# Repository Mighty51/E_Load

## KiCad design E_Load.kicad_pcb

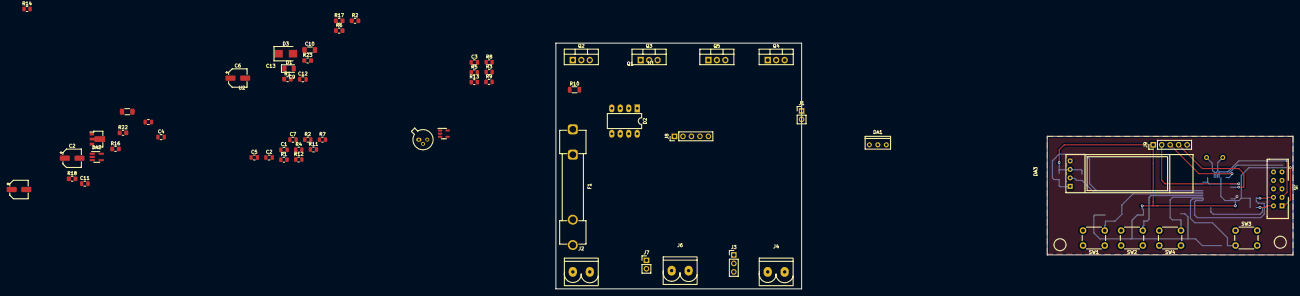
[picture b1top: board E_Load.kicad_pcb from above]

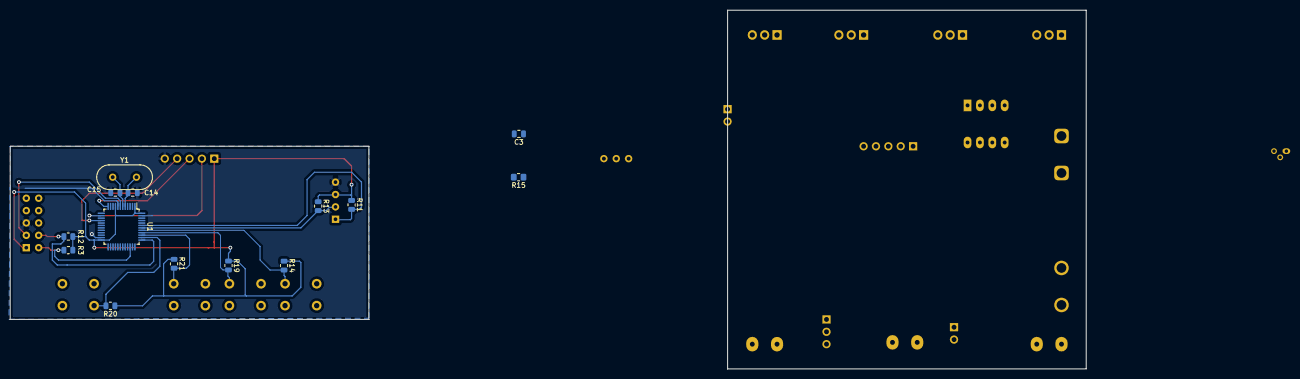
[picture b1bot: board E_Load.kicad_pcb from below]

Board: 2 copper layers, 76 parts (14 on the bottom side), 38 nets.

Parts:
C1, C3#2: 0,1мкФ; C_0805_2012Metric
C2: 4мкФ; C_0805_2012Metric
C2#2: 4.7u; CP_Elec_5x5.3
C3, C5, C7, C9, C11, C12: C; C_0805_2012Metric
C4: 47p; C_0805_2012Metric
C6: C_Polarized; CP_Elec_5x5.3
C8: C_Polarized; CP_Elec_5x5.4
C10, C13: C_Polarized; C_1206_3216Metric_Pad1.33x1.80mm_HandSolder
C14, C15: 8p; C_0805_2012Metric
D1: 6.8В; D_1206_3216Metric
D2: LM358; DIP-8_W7.62mm_LongPads
D3: SM6T15A; D_SMB
DA1: LM217t; TO-220
DA2: INAx180; SOT-23-5_HandSoldering
DA3: SSD1306_display; Display_SSD1306
F1: Fuse; Fuseholder_Clip-6.3x32mm_Littelfuse_102071_Inline_P34.70x7.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
J1: FAN_Connector; PinHeader_1x02_P2.54mm_Vertical
J2: Load; Conn_x2
J3: Джампер; PinHeader_1x03_P2.54mm_Vertical
J4: External_VCC; Conn_x2
J5: Conn_ARM_SWD_TagConnect_TC2030-NL; PWD_10pin_Conn
J6: Voltage_Sens; Conn_x2
J7: Jamper; PinHeader_1x02_P2.54mm_Vertical
J8: Conn_01x05_Female; PinHeader_1x05_P2.54mm_Vertical
J9: Conn_01x05_Male; PinHeader_1x05_P2.54mm_Vertical
Q1: КТ3102; TO-18-3
Q2, Q3, Q4, Q5: IRF740; TO-220-3_Vertical
R1, R9: 1кОм; R_0805_2012Metric
R1#2, R15, R22, R23: 1k; R_0805_2012Metric_Pad1.20x1.40mm_HandSolder
R2: 51Ом; R_0805_2012Metric
R2#2: 9.1k; R_0805_2012Metric_Pad1.20x1.40mm_HandSolder
R3: 450Ом; R_0805_2012Metric
R3#2, R11#2, R12#2, R13#2, R14#2, R19, R20, R21: 10k; R_0805_2012Metric
R4: 300Ом; R_0805_2012Metric
R5, R7, R8: 100Ом; R_0805_2012Metric
R6: 100Ом; R_0805_2012Metric_Pad1.20x1.40mm_HandSolder
R10: 0,1Ом; R_1206_3216Metric
R11: 0,01Ом(шунт); R_0805_2012Metric
R12, R13: 500кОм; R_0805_2012Metric
R14: R; R_0805_2012Metric
R16: 2.7k; R_0805_2012Metric_Pad1.20x1.40mm_HandSolder
R17: 240; R_0805_2012Metric_Pad1.20x1.40mm_HandSolder
R18: 390; R_0805_2012Metric_Pad1.20x1.40mm_HandSolder
SW1, SW2, SW3, SW4: SW_MEC_5E; SW_PUSH_6mm
U1: LM321; SOT-23-5
U1#2: STM32F051C6Tx; LQFP-48_7x7mm_P0.5mm
U2: L78L12_SOT89; SOT-89-3
Y1: Crystal; Crystal_HC49-4H_Vertical

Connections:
+3.3V: C7.1, C8.1, DA1.2 (Vout), DA2.5 (VSS), DA3.3 (Vcc), J5.1 (VCC), J8.1, J9.1, R3#2.1, R11#2.1, R12#2.1, R13#2.1, R14#2.1, R17.1, R19.1, R20.1, R21.1, U1#2.1 (VBAT), U1#2.9 (VDDA), U1#2.24 (VDD), U1#2.48 (VDD)
+12V: C4.2, C11.1, C13.1, D2.8, J1.1, R1.1, U1.5 (V+), U2.1 (OUT)
Button+: R14#2.2, SW1.2, U1#2.41 (PB5)
Button-: R19.2, SW2.2, U1#2.40 (PB4)
ButtonEn: R20.2, SW3.2, U1#2.38 (PA15)
ButtonMode: R21.2, SW4.2, U1#2.39 (PB3)
CurrentSens: DA2.1 (OUT), J8.4, J9.4, U1#2.16 (PA6)
GND: C1.2, C2.2, C2#2.2, C3.2, C3#2.2, C4.1, C5.2, C6.2, C7.2, C8.2, C9.2, C10.2, C11.2, C12.2, C13.2, C14.1, C15.2, D1.2 (A), D2.4, D3.2 (A2), DA2.2 (GND), DA3.4 (GND), J1.2, J2.2, J4.2, J5.5 (GND), J6.2, J8.5, J9.5, Q1.1 (E), Q2.3 (S), Q3.3 (S), Q4.3 (S), Q5.3 (S), R2#2.1, R3.2, R9.2, R11.1, R13.1, R15.2, R18.2, U1.2 (V-), U1#2.8 (VSSA), U1#2.23 (VSS), U1#2.47 (VSS), U2.2 (GND)
I2C_SCL: DA3.2 (SCL), R13#2.2, U1#2.42 (PB6)
I2C_SDA: DA3.1 (SDA), R11#2.2, U1#2.43 (PB7)
unnamed: C1.1, D2.3 (+), R22.2, U1.1 (+)
unnamed: C3#2.1, D2.5 (+), R23.2
unnamed: C14.2, U1#2.5 (PF0), Y1.2
unnamed: C15.1, U1#2.6 (PF1), Y1.1
unnamed: D1.1 (K), R4.2, R5.1, R6.1, R7.1, R8.1
unnamed: D2.1, R4.1, R14.1
unnamed: D2.2 (-), R9.1
unnamed: D2.6 (-), R15.1, R16.1
unnamed: DA1.1 (ADJ), R17.2, R18.1
unnamed: F1.2, J2.1
unnamed: J3.3, J4.1
unnamed: Q1.2 (B), R12.1, R13.2
unnamed: Q1.3 (C), R2.2, R3.1
unnamed: Q2.1 (G), R5.2
unnamed: Q3.1 (G), R6.2
unnamed: Q4.1 (G), R7.2
unnamed: Q5.1 (G), R8.2
unnamed: R1.2, R2.1
Res: J5.3 (~RESET), U1#2.7 (NRST)
SWCLK: J5.4 (SWCLK), R12#2.2, U1#2.37 (PA14)
SWDIO: J5.2 (SWDIO), R3#2.2, U1#2.34 (PA13)
Shunt: C2#2.1, DA2.4 (IN-), Q2.2 (D), Q3.2 (D), Q4.2 (D), Q5.2 (D), R10.2
Vcc: C5.1, C6.1, C9.1, C10.1, DA1.3 (Vin), J3.2, U2.3 (IN)
Vdac_reg: J8.2, J9.2, R23.1, U1#2.14 (PA4)
Vin_div: C12.1, J8.3, J9.3, R1#2.1, R2#2.2, U1#2.12 (PA2)
Vload: C2.1, D3.1 (A1), DA2.3 (IN+), F1.1, J3.1, J7.1, R10.1, R12.2
VoltageSens: J6.1, J7.2, R1#2.2
Vreg: D2.7, R16.2, R22.1
